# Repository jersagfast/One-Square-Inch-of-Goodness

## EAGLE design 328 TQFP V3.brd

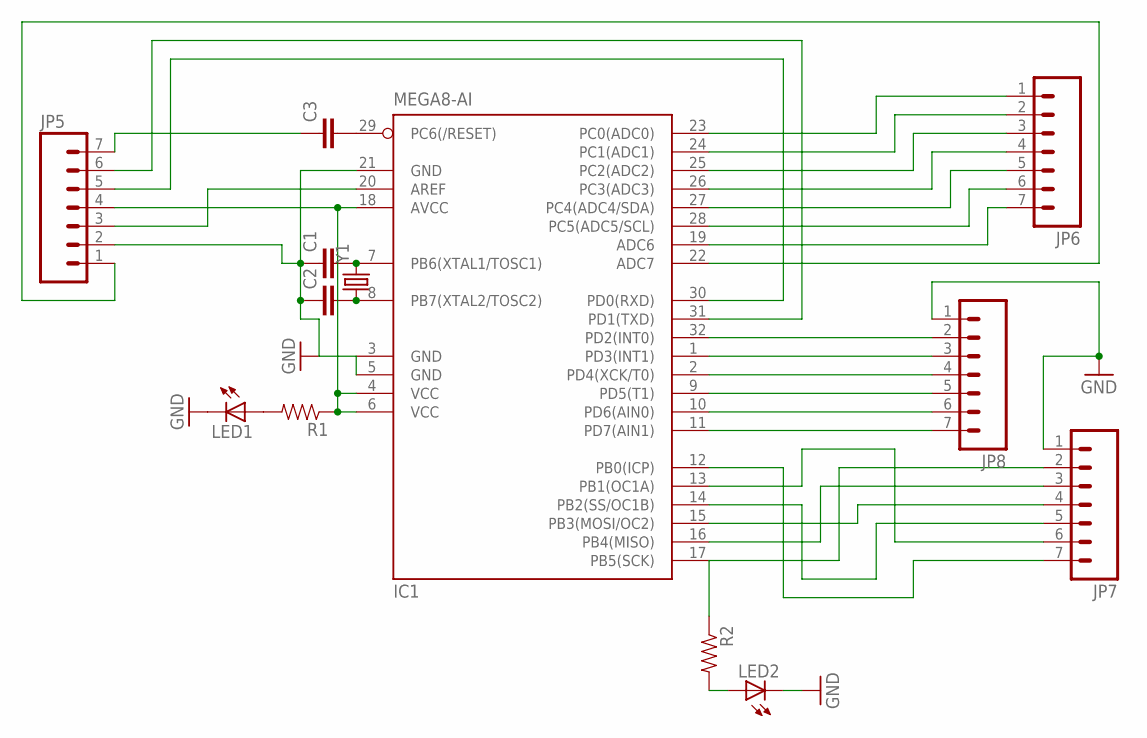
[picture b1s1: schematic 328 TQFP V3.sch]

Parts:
C1, C2, C3: CAP0603-CAP; 0603-CAP
IC1: MEGA8-AI; TQFP32-08
JP5, JP6, JP7, JP8: M07; 1X07
LED1, LED2: LED0603; LED-0603
R1, R2: RESISTOR0603-RES; 0603-RES
Y1: CRYSTAL5X3; CRYSTAL-SMD-5X3

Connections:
GND: C1.1, C2.1, IC1.3 (GND), IC1.5 (GND), IC1.21 (GND), JP5.2, JP7.1, JP8.1, LED1.C, LED2.C
unnamed: LED1.A, R1.2
unnamed: IC1.4 (VCC), IC1.6 (VCC), IC1.18 (AVCC), JP5.4, R1.1
unnamed: C1.2, IC1.7 (PB6(XTAL1/TOSC1)), Y1.3 (2)
unnamed: C2.2, IC1.8 (PB7(XTAL2/TOSC2)), Y1.1
unnamed: C3.1, JP5.7
unnamed: IC1.20 (AREF), JP5.3
unnamed: C3.2, IC1.29 (PC6(/RESET))
unnamed: IC1.31 (PD1(TXD)), JP5.6
unnamed: IC1.30 (PD0(RXD)), JP5.5
unnamed: IC1.23 (PC0(ADC0)), JP6.1
unnamed: IC1.24 (PC1(ADC1)), JP6.2
unnamed: IC1.25 (PC2(ADC2)), JP6.3
unnamed: IC1.26 (PC3(ADC3)), JP6.4
unnamed: IC1.27 (PC4(ADC4/SDA)), JP6.5
unnamed: IC1.28 (PC5(ADC5/SCL)), JP6.6
unnamed: IC1.19 (ADC6), JP6.7
unnamed: IC1.22 (ADC7), JP5.1
unnamed: IC1.17 (PB5(SCK)), JP7.2, R2.1
unnamed: IC1.16 (PB4(MISO)), JP7.3
unnamed: IC1.15 (PB3(MOSI/OC2)), JP7.4
unnamed: IC1.14 (PB2(SS/OC1B)), JP7.5
unnamed: IC1.13 (PB1(OC1A)), JP7.6
unnamed: IC1.12 (PB0(ICP)), JP7.7
unnamed: IC1.11 (PD7(AIN1)), JP8.7
unnamed: IC1.10 (PD6(AIN0)), JP8.6
unnamed: IC1.9 (PD5(T1)), JP8.5
unnamed: IC1.2 (PD4(XCK/T0)), JP8.4
unnamed: IC1.1 (PD3(INT1)), JP8.3
unnamed: IC1.32 (PD2(INT0)), JP8.2
unnamed: LED2.A, R2.2

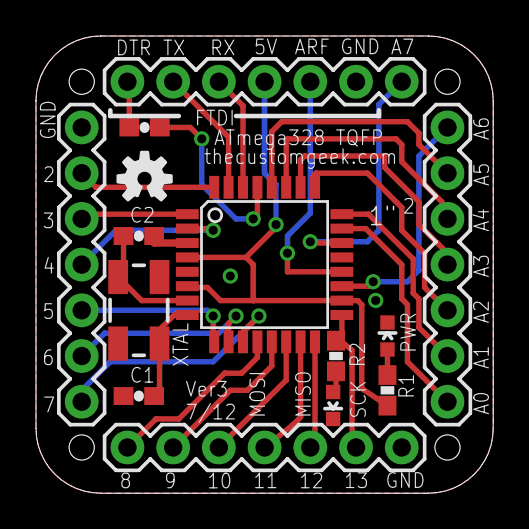
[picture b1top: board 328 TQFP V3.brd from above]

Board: 2 copper layers, 25.4 x 25.4 mm, 15 parts (1 on the bottom side), 31 nets.

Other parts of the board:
U$1, U$2: OSHW-LOGO-S

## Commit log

2012-07-09 Square inch Arduino board
2012-08-08 Added ZIP file of berbers.
2012-08-08 Added latest version - added values in schematic.
